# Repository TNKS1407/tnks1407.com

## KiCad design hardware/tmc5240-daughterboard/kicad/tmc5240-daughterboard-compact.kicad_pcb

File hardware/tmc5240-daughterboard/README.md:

# TMC5240 ステッピングモータ駆動 子基板 — 設計書 Rev.2a

JLCPCB 発注（PCBA、LCSC 在庫部品）前提。ホストは Raspberry Pi Pico（3.3V / SPI）。

**Rev.2 変更点:** エンコーダ後付け対応（J4 追加、ENCA/B/N を GND 直結→ヘッダ＋10k プルダウンに変更）、UART_EN を GND 直結→ハンダジャンパ SJ1（既定 GND=SPI）に変更。

**Rev.2a 変更点（レイアウト確定に伴う）:**
- **KiCad 基板レイアウト完成**（`kicad/`、60×42mm 4層、**DRC エラー 0・未接続 0**）。製造データは `fab/`。
- **J1 ピン並び変更**: 7〜11 番を `REFL, REFR, ENN, DIAG0, DIAG1` の順に（配線交差の完全回避のため）。
- **J3 ピン並び変更**: `1:OUT1A, 2:OUT2A, 3:OUT2B, 4:OUT1B`（A1 A2 B2 B1）。コイルB の2線は太い配線を表層で交差なく引くための入替。結線はシルク表記に従えば従来と等価。
- C10〜C13（1nF EMC対策、DNP可）は**基板にパターンを設けない**判断とした（必要になった事例が出たら Rev.3 で追加）。

| 項目 | 値 |
|---|---|
| モータ | バイポーラ2相、定格 1.5 A/相、巻線 2.8 Ω |
| 電源 VS | 24 V 単一入力、想定最大 2 A |
| ホスト I/F | 4線 SPI（UART_EN = GND で選択） |
| VCC_IO | 3.3 V（Pico 3V3） |
| コイル電流 | 1.5 A RMS（R_IREF 12 kΩ + GLOBALSCALER=181 + IRUN=31） |
| モード | StealthChop2 ＋ StallGuard4 センサレス原点出し |
| 成果物 | `schematic.svg`（回路図）, `bom_jlcpcb.csv`（JLCPCB用BOM）, 本書 |

## Rev.0 ドラフトからの訂正（データシート・実設計クロスチェックの結果）

初版の一般論ベースの想定から、以下を**訂正**した。根拠は ADI 公式データシート（検索抽出）、公式 TMC-API レジスタ定義、および独立した2つの公開リファレンス設計（KiCad ネットリストを直接照合）。

1. **VSA ピンは存在しない** → VSA 用 RC/フェライトフィルタを削除。アナログ系は AGND ピンのみ分離。
2. **内蔵レギュレータは 1.8V コア（VDD1V8 ピン）**であり 5V ではない → 2.2 µF を AGND へ。出力専用・負荷接続禁止。
3. **チャージポンプのリザーバは VCP–VS 間 1.0 µF**（100nF ではない）。フライングは CPO–CPI 間 22 nF/50V。
4. **SD_MODE / SPI_MODE ピンは存在しない**。インターフェース選択は UART_EN のみ（GND=SPI）。STEP/DIR ピン自体が無い（内蔵ランプジェネレータ専用）。
5. **SLEEPN（内部プルダウン）を H に吊る必要がある**。唯一の高電圧トレラント制御ピン。本設計では 3V3 へ直結。
6. **CSN は内部プルダウン**（UART アドレスストラップ兼用）→ MCU ブート中の誤選択防止に 10 kΩ プルアップを追加。
7. RDSon 実測値（HS 0.12 Ω + LS 0.11 Ω @3A レンジ）により**損失見積を 2.7 W → 約 1.0〜1.5 W に下方修正**。
8. パッケージは **TQFN-32 5×5（TMC5240ATJ+）と TSSOP-38（AUU+）のみ**。TQFP32 は存在しない。JLCPCB 在庫があるのは TQFN-32 リール品。

## 1. 電流設計（計算根拠）

```
IFS = KIFS / R_IREF            KIFS: 1Aレンジ 11.75, 2Aレンジ 24, 3Aレンジ 36 [A·kΩ]
I_RMS = (GLOBALSCALER/256) × ((CS+1)/32) × IFS/√2
```

- 目標 1.5 A RMS → ピーク 1.5×√2 = **2.12 A** → 2A レンジ（最大 2.0 A ピーク）では不足 → **3A レンジ**。
- **R_IREF = 12 kΩ ±1%** → IFS = 36/12 = **3.0 A**（IREF ピン電圧 ≈0.9 V、許容 12–60 kΩ※下記「要確認」参照）。
- CS(IRUN) = 31 固定（CoolStep の動作余地を確保）、GLOBALSCALER で合わせ込み:
  `1.5 = (GS/256) × 1 × 3.0/√2 → GS = 256×0.7071 ≈ 181 (0xB5)` — 推奨帯 128–255 内。
- IFS 3.0 A はデバイス定格（2 A RMS / 3 A ピーク）の範囲内、運転 1.5 A RMS も連続定格内。

**レジスタ初期値（TMC-API 名）**

| レジスタ | 値 | 意味 |
|---|---|---|
| DRV_CONF.CURRENT_RANGE | 2 (=3A) | フルスケールレンジ |
| GLOBALSCALER | 181 | 3.0A×0.707 → 2.12A ピーク |
| IHOLD_IRUN.IRUN | 31 | 1.5 A RMS |
| IHOLD_IRUN.IHOLD | 10 | 保持 ≈0.5 A RMS（発熱低減、要調整） |
| GCONF.en_pwm_mode | 1 | StealthChop2 |
| GCONF.diag0_int_pushpull / diag1_poscomp_pushpull | 0 | オープンドレイン（外部10kプルアップ前提） |

## 2. 回路各部（`schematic.svg` 対応）

### ① 電源入力・保護
- J2(+24V) → F1 PPTC 3A/33V → Q1 P-MOSFET 逆接保護（D=入力, S=負荷, G=R8 10k→GND, D2 BZT52C12 で |VGS| を 12V にクランプ）→ VS。
- D1 SMBJ33A（33V standoff）で VS–GND をクランプ。C1 100 µF/35V バルク。
- Q1 は SOT-23 で −40V/−3A（60 mΩ）。24V系で −30V 品（AO3401A 等）は TVS クランプ時に耐圧不足になるため不可。電流余裕が欲しい場合は AOD4185（TO-252, −40V/−40A）へ差し替え。

### ② デカップリング
- VS: 1 µF + 100 nF を VS ピン2グループ（pin17 側 / pin20-21-24 側）の直近に各1組（C2/C4, C3/C5）。
- VCC_IO: 100 nF（C9）。VDD1V8: 2.2 µF（C8, AGND へ）。
- モータ出力 OUT1A/2A/1B/2B に 1 nF（C10–13, EMC対策, DNP可）。

### ③ チャージポンプ
- CPO–CPI: 22 nF/50V（C6）。VCP–VS: 1 µF（C7, **VS ピン直近に配置** — 誘導性ピーク回避のためデータシート指示）。

### ④ ロジック
- UART_EN → **SJ1（3パッドハンダジャンパ、既定 GND側ブリッジ = 4線SPI）**。3V3 側に付け替えると1線UARTモード。CLK=GND（内蔵発振 12.5 MHz ±5%、SPI クロック上限 10 MHz）。
- AIN 未使用 → GND。OV ピン未使用 → 開放（過電圧クランプFETは未実装）。
- プルアップ 10k×4: CSN / ENN(DRV_ENN) / DIAG0 / DIAG1（DIAG はオープンドレイン既定のため必須）。
- プルダウン 10k×2: REFL / REFR（未接続時のレベル確定。SW_MODE で極性設定可）。

### ⑤ エンコーダ（後付け対応）
- ENCA/ENCB/ENCN を J4（2.54mm 1×5: 3V3 / A / B / N / GND）へ引き出し。**未接続時は R9〜R11 の 10k プルダウンでレベル確定**（フロート禁止のため）。
- 対応エンコーダは **3.3V ロジック（VCC_IO ドメイン）の ABN インクリメンタル**。5V 出力品はレベル変換が必要。
- 使うときのレジスタ: `ENCMODE`(0x38) で極性/クリア条件、`ENC_CONST`(0x3A) にエンコーダ分解能↔マイクロステップ換算、実位置は `X_ENC`(0x39)。N チャネルで StallGuard 原点出しより高精度なホーミングも可能。

### UART について（設計判断）
- Pico と1対1の本構成では **SPI を正式採用**。全二重・10MHz・毎応答ステータス付きで、StealthChop2/StallGuard4 の全機能が使える。
- TMC5240 の UART は1線半二重で、利点は配線削減と多軸デイジーチェーン（CSN/SCK/SDI がアドレスストラップ AD2/AD1/AD0 兼用）。単基板では利点なし。
- ただし選択は UART_EN ピン1本なので、**SJ1 により追加部品ゼロで将来切替可能**にした。UART に切り替えた場合、J1 の SDI ピンが1線データ、CSN/SCK のプルアップ/プルダウン状態がノードアドレスになる点に注意。

### コネクタ

**J1 2.54mm 1×12（Pico 接続）**

| ピン | 信号 | Pico |
|---|---|---|
| 1 | GND | GND |
| 2 | 3V3 | 3V3(OUT) — VCC_IO 用。モータ電源とは別系統 |
| 3 | SCK | GP18 (SPI0 SCK) |
| 4 | SDI (MOSI) | GP19 (SPI0 TX) |
| 5 | SDO (MISO) | GP16 (SPI0 RX) |
| 6 | CSN | GP17 |
| 7 | REFL | 原点SW（任意） |
| 8 | REFR | 原点SW（任意） |
| 9 | ENN | 任意 GPIO（L=駆動許可） |
| 10 | DIAG0 | 任意 GPIO（割込/StallGuard） |
| 11 | DIAG1 | 任意 GPIO |
| 12 | GND | GND |

> ピン並びは Rev.2a レイアウトの配線順に合わせた確定値（交差回避）。

**J2** 5.08mm 2P: +24V / GND　**J3** 5.08mm 4P: `1:OUT1A / 2:OUT2A（コイルA）/ 3:OUT2B / 4:OUT1B（コイルB）`（シルク: A1 A2 B2 B1）

**J4 2.54mm 1×5（エンコーダ、後付け可）**

| ピン | 信号 | 備考 |
|---|---|---|
| 1 | 3V3 | エンコーダ電源（3.3V ロジック品のみ） |
| 2 | ENCA | A相 |
| 3 | ENCB | B相 |
| 4 | ENCN | N（インデックス） |
| 5 | GND | — |

## 3. ネットリスト

| ネット | 接続 |
|---|---|
| +24V_IN | J2.1, F1.1 |
| 24V_F | F1.2, Q1.D |
| VS | Q1.S, D2.K, D1.K, C1.+, C2.1, C3.1, C4.1, C5.1, C7.2, U1.17, U1.20, U1.21, U1.24 |
| Q1_G | Q1.G, R8.1, D2.A |
| 3V3 | J1.2, J4.1, U1.5(VCC_IO), U1.25(SLEEPN), R2.1, R3.2, R4.2, R5.2, C9.1, SJ1.3 |
| SCK | J1.3, U1.27 |
| SDI | J1.4, U1.28 |
| SDO | J1.5, U1.29 |
| CSN | J1.6, U1.26, R2.2 |
| ENN | J1.9, U1.9(DRV_ENN), R3.1 |
| DIAG0 | J1.10, U1.11, R4.1 |
| DIAG1 | J1.11, U1.12, R5.1 |
| REFL | J1.7, U1.31, R6.1 |
| REFR | J1.8, U1.32, R7.1 |
| ENCA | J4.2, U1.8, R9.2 |
| ENCB | J4.3, U1.7, R10.2 |
| ENCN | J4.4, U1.6, R11.2 |
| UART_EN | U1.10, SJ1.2（中央パッド） |
| IREF | U1.1, R1.2 |
| VDD1V8 | U1.3, C8.2 |
| CPO | U1.15, C6.2 |
| CPI | U1.14, C6.1 |
| VCP | U1.16, C7.1 |
| OUT1A | U1.23, J3.1 |
| OUT2A | U1.22, J3.2 |
| OUT2B | U1.19, J3.3 |
| OUT1B | U1.18, J3.4 |
| GND | J2.2, J1.1, J1.12, J4.5, D1.A, C1.−, C2–C5.2, C8.1(AGND経由), C9.2, R1.1, R6.2, R7.2, R8.2, R9.1, R10.1, R11.1, SJ1.1（既定ブリッジ側）, U1.2(AIN), U1.4(AGND), U1.30(CLK), U1.EP, H1–H3 |

## 4. 発熱見積

- 導通損: 2相 × 1.5² × (0.12+0.11) Ω ≈ **1.04 W**。スイッチング・コア込みで **約 1.3〜1.5 W**。
- **θJA 実値（自己レビューで確認）: TQFN32 = 29 ℃/W（4層 JEDEC 基板）/ 47 ℃/W（1層）、θJC 1.7 ℃/W**。
  - Rev.2a（60×42, 4層）: JEDEC 基板よりやや小さいので実効 30〜38 ℃/W → ΔT ≈ 40〜55 ℃、室温で Tj ≈ 75〜80 ℃ ✓
  - Rev.2b（50×36, 4層）: 実効 ~40〜47 ℃/W → ΔT ≈ 55〜65 ℃。1.5A RMS 連続は成立圏内だが余白薄
- いずれも **EP 直下サーマルビア9本＋GND ベタ**を実装済み。停止時は IHOLD=10 で電流を落とす。

## 5. レイアウト注意

- EP（露出パッド）= パワー GND。直下にサーマルビア ≥9 本、裏面ベタへ。
- C7（VCP–VS）と C6（CPO–CPI）は該当ピン直近・最短ループ。
- R1（IREF）はピン1直近、GND リターン最短、モータ配線から離す（電流精度に直結）。
- C2/C4 と C3/C5 は VS ピンの2グループにそれぞれ配置。C1 はその外側。
- AGND（pin4）と C8 のリターンは静かな GND 経由で EP ベタへ（モータ電流経路と分ける）。
- OUT 配線は太く短く。J2/J3（24V系）と J1（3.3V系）は物理的に分離。

## 5.5 KiCad レイアウト（Rev.2a、`kicad/` と `fab/`）

- **基板**: 60 × 42 mm、**4層**（L1: 信号＋GNDベタ / L2: GND 全面 / L3: 3V3＋VS プレーン＋GND / L4: 一部信号＋GNDベタ）。M2.5 マウント穴 ×3（GND接続）。
- **検証**: KiCad 7 DRC で **エラー 0・未接続パッド 0**（クリアランス 0.15mm、最小ビア 0.4/0.2 — JLCPCB 4層の標準能力内）。
- **生成方法**: `kicad/generate_pcb.py` が基板を完全生成（`python3 generate_pcb.py`）。手修正せずスクリプトを変更して再生成する運用。
- **主要配置**: J1(Pico)左端 / J2(24V)上左 / 保護回路（F1→Q1→D1→C1）上辺 / U1 中央（EP 直下サーマルビア9本） / J3(モータ)右端 / J4(エンコーダ)＋SJ1 下辺。
- **電源**: 24V入力 2.0mm 幅、モータ出力はエスケープ 0.25→0.5→1.0mm 段階拡幅、VS/3V3 は内層プレーン給電。
- **`fab/` の内容**:
  - `tmc5240-daughterboard_gerbers.zip` — JLCPCB にそのままアップロードする製造データ（4層）
  - `bom_jlcpcb_pcba.csv` / `cpl_jlcpcb.csv` — PCBA 用 BOM・配置データ
- **発注手順**: ①zip をアップロード → 4 Layers を確認 ② PCBA(Economic) を選択、BOM/CPL を投入 ③ 部品照合で **U1 の在庫確保**と**回転（特に U1/Q1/D1/D2 の向き）を必ずプレビューで確認**（KiCad→JLCPCB の回転規約差は要目視）。
- **PCBA 対象外**: J4（C番号未確定 → 手半田推奨）、SJ1（銅箔のみ）、H1–H3（穴）。J1/J2/J3 は THT — Economic PCBA の THT 対応か手半田かを選択。

## 5.6 Rev.2b コンパクト版（50×36mm、`kicad/generate_pcb_compact.py`）

Rev.2a（60×42）の**トポロジ・回路・J1/J3 ピン配列をそのまま**に、面積を −50% した派生版。**KiCad 7 DRC エラー 0・未接続 0**。

- **サイズの意味**: JLCPCB の**4層最安ティア（50×50mm 以内）に収まる**。60mm 幅の Rev.2a はティア超えだったため、小型化がそのままコストダウンになる
- **全配線 45° 面取り**（`track()` ヘルパーが直角コーナーを自動チャンファ）
- 変更点: D1(TVS) は J3 上の空き地へ移動（SMBJ33A のまま）、マウント穴は M2×2（右下・左下）、C10–13 相当は引き続き非実装
- **放熱トレードオフ**: 銅面積半減で θJA ≈ 45 K/W 見込み（Rev.2a 比 +10）。1.5A RMS 連続は成立圏内だが余白減。**IHOLD 低減運用を推奨**、連続高負荷なら Rev.2a を選ぶ
- 製造データ: `kicad/fab-compact/`（ガーバー zip / BOM / CPL）。どちらを発注するかで `fab/`（Rev.2a）と使い分け

## 6. JLCPCB 発注メモ

- **U1 の在庫が薄い**（2026-07 時点 約240個）→ 発注前に JLCPCB のプライベートライブラリで部品確保推奨。
- TMC2240（C7429724, 在庫潤沢・安価）は**ピン互換ではない**（STEP/DIR 型でランプジェネレータ非搭載）。代替にする場合は回路・ソフト両方の再設計が必要。
- パッシブはほぼ Basic 部品（実装費安）。Extended は U1/Q1/D1/D2/F1/C1/コネクタ類。
- J1/J2/J3 は THT → JLCPCB の「Standard PCBA (THT対応)」を選択するか、手半田にするなら BOM から除外。
- Basic/Extended 区分と在庫は変動する。**発注直前に JLCPCB の BOM ツールで再確認**。

## 7. 設計レビュー チェックリスト

- [ ] R_IREF=12kΩ 1% / CURRENT_RANGE=3A / GLOBALSCALER=181 / IRUN=31 → 1.5 A RMS の整合
- [ ] CPO–CPI 22nF・VCP–VS 1µF がピン直近か
- [ ] VDD1V8 に 2.2µF（AGND へ）、負荷を繋いでいないか
- [ ] SLEEPN が 3V3 に接続されているか（内部プルダウンのため開放不可）
- [ ] SJ1 が GND 側ブリッジ（SPI）で製造されるか（銅箔ブリッジ or 製造時ハンダ指示）、CLK=GND（内蔵OSC）か
- [ ] DIAG0/1・CSN・ENN に 10k プルアップ、REFL/REFR・ENCA/B/N に 10k プルダウン
- [ ] エンコーダは 3.3V ロジック品か（5V 品はレベル変換要）
- [ ] TVS クランプ電圧が VS 絶対最大（38V）を超える条件を理解しているか（§8 参照。大回生用途は OV クランプ追加）／Q1 耐圧 −40V 以上か
- [ ] EP サーマルビア・GND ベタ・IHOLD 低減の放熱3点セット
- [ ] 発注直前の在庫・Basic/Extended 再確認（特に U1）

## 8. 自己レビュー結果（2026-07-02 実施）と残る未確認事項

データシート PDF 原本は取得経路が全て遮断されたため、**到達可能な一次情報での機械照合レビュー**を実施した。使用ソース: ADI 公式レジスタ定義（TMC-API `TMC5240_HW_Abstraction.h`）、Klipper 公式ドライバ（`tmc2240.py`、同一電流アーキテクチャ）、独立した実設計3ソースのシンボル/回路図（RPZ-Stepper 系 .kicad_sym、equilibot、MIT MediaLab pan-tilt）。

### 検証済み（機械照合で確認）

| 項目 | 結果 |
|---|---|
| U1 ピン配置（33ピン） | **3つの独立ソースと全一致**（スクリプトで pin番号→名称を突き合わせ） |
| 電流設定式 | Klipper 実装と完全一致: `KIFS=[11.75,24,36]A·kΩ`, `I_RMSmax=KIFS/Rref/√2`, `GS=round(256·I/I_RMSmax)` → **12kΩ+3Aレンジ+GS=181 で 1.500A RMS（丸めまで一致）**。Rref=12kΩ は Klipper の既定値でもある |
| GLOBALSCALER 制約 | 公式ヘッダ記載と一致（1–31 禁止、>128 推奨、0=フルスケール） |
| 標準回路定数 | 22nF(CPO–CPI)・2.2µF(VDD1V8)・1µF(VCP)・IREF 12k/13k を実設計2件で確認 |
| **θJA/θJC 実値** | TQFN32: **29 ℃/W（4層 JEDEC 基板）/ 47 ℃/W（1層）、θJC 1.7 ℃/W**。§4 の見積（35〜45）は安全側で妥当 |
| VS 絶対最大 | **38 V**（絶対最大表の断片「CPO ≤ min(44, VS+6)V」の44上限から逆算、姉妹品 TMC2240=38V とも一致。直接記載の確認は未） |
| Rev.2a ⇔ Rev.2b | 全112パッドのネット割当を diff、**電気的に同一**（差分は H3 削除と R2 のパッド順のみ＝抵抗なので無影響） |
| Q1 ピン配置 | SOT-23 単体 P-MOSFET は業界横断で 1=G/2=S/3=D（ST/onsemi/MCC で確認）。基板はこの通り |

### レビューで見つかった問題（正直に）

**⚠ TVS（SMBJ33A）は高エネルギーサージに対して完全ではない。** VS 絶対最大 38V に対し、SMBJ33A のクランプ電圧は定格サージ電流時 **最大 53.3V** — ESD や小サージには有効だが、大きな誘導性サージ／モータ回生では 38V を超えるおそれがある。スタンドオフを下げても（SMBJ30A 等）クランプは 38V を下回らないため、**TVS 単体では構造的に解決しない**（36V級ドライバ＋24V系の一般的な妥協点）。データシートが想定する本来の対策は **OV ピン＋外付け N-FET クランプ**（MIT MediaLab 設計は実装済み、本設計は未実装・OV開放）。

**運用条件**: 安定化24V電源・回生エネルギー小（通常のNEMA17位置決め用途）なら現状で実用可。長い減速で大きな回生が出る用途・電源が不安定な環境では **Rev.3 で OV クランプ回路（N-FET+抵抗2本+ショットキー）の追加を推奨**。

### 残る未確認（PDF 原本が読めたら潰す）

1. VS 絶対最大 38V の直接記載確認（傍証は強い）
2. R_IREF 許容帯の正式値（12–60k か 12–24k か。12kΩ はどちらでも適合）
3. S-LP2408LT1G 固有データシートのピン配置（業界慣例とは一致）
4. C10–13 用 C1588 の Basic 区分

### 根拠資料

- [TMC5240 データシート (ADI)](https://www.analog.com/media/en/technical-documentation/data-sheets/tmc5240.pdf)（検索抽出）
- [TMC-API TMC5240 レジスタ定義 (ADI 公式 GitHub)](https://github.com/analogdevicesinc/TMC-API/blob/master/tmc/ic/TMC5240/TMC5240_HW_Abstraction.h)
- [電流設定の考え方 (ADI EngineerZone)](https://ez.analog.com/other-products/w/documents/32673/)
- リファレンス設計: [benjibst/equilibot](https://github.com/benjibst/equilibot), [mitmedialab/generic-pan-tilt-pcb](https://github.com/mitmedialab/generic-pan-tilt-pcb)（KiCad ネットリスト照合）
- [TMC5240ATJ+T @LCSC C7494373](https://www.lcsc.com/product-detail/Motor-Driver-ICs_TRINAMIC-Motion-Control-GmbH-TMC5240ATJ-T_C7494373.html) / [@JLCPCB](https://jlcpcb.com/partdetail/8557215-TMC5240ATJT/C7494373)

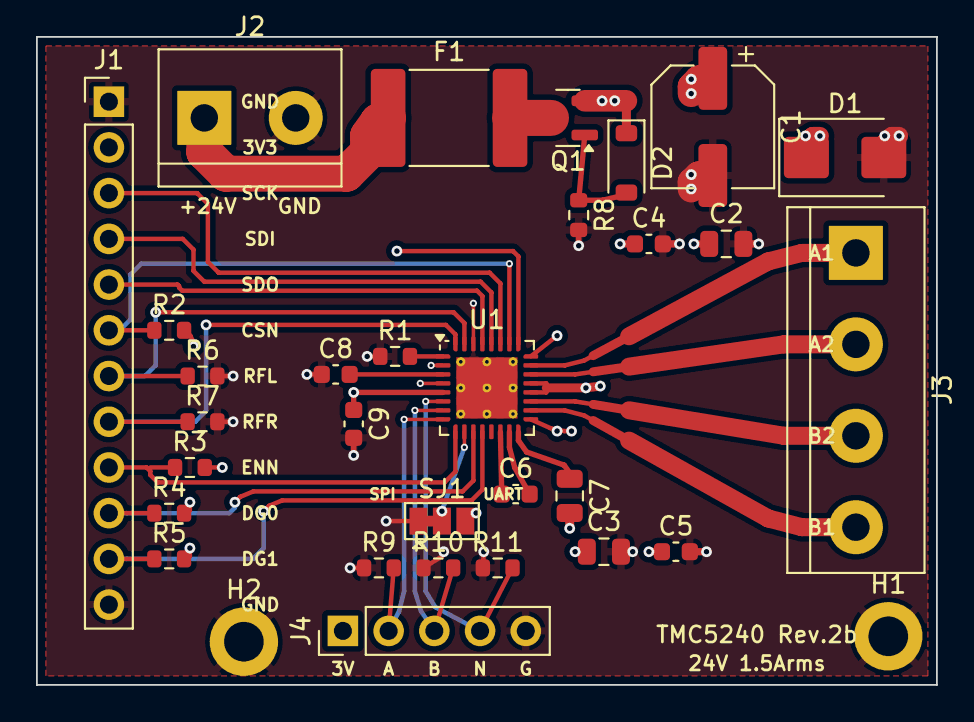
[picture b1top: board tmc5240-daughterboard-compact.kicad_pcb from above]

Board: 4 copper layers, 50.0 x 36.0 mm, 32 parts (0 on the bottom side), 28 nets.

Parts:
C1: 100uF/35V; CP_Elec_6.3x7.7
C2, C3, C7: 1uF/50V; C_0805_2012Metric
C4, C5: 100nF/50V; C_0603_1608Metric
C6: 22nF/50V; C_0603_1608Metric
C8: 2.2uF; C_0603_1608Metric
C9: 100nF; C_0603_1608Metric
D1: SMBJ33A; D_SMB
D2: BZT52C12; D_SOD-123
F1: PPTC 3A/33V; Fuse_2920_7451Metric
H1, H2: M2; MountingHole_2.2mm_M2_DIN965_Pad
J1: Pico 1x12; PinHeader_1x12_P2.54mm_Vertical
J2: +24V IN; TerminalBlock_bornier-2_P5.08mm
J3: MOTOR; TerminalBlock_bornier-4_P5.08mm
J4: ENC 1x5; PinHeader_1x05_P2.54mm_Vertical
Q1: S-LP2408LT1G; SOT-23
R1: 12k 1%; R_0603_1608Metric
R2, R3, R4, R5, R6, R7, R8, R9, R10, R11: 10k; R_0603_1608Metric
SJ1: SPI/UART; SolderJumper-3_P1.3mm_Bridged12_Pad1.0x1.5mm
U1: TMC5240ATJ+T; TQFN-32-1EP_5x5mm_P0.5mm_EP3.4x3.4mm_ThermalVias

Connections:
3V3: C9.1, J1.2, J4.1, R2.2, R3.2, R4.2, R5.2, SJ1.3, U1.5, U1.25
24V_F: F1.2, Q1.3
+24V_IN: F1.1, J2.1
CPI: C6.1, U1.14
CPO: C6.2, U1.15
CSN: J1.6, R2.1, U1.26
DIAG0: J1.10, R4.1, U1.11
DIAG1: J1.11, R5.1, U1.12
ENCA: J4.2, R9.2, U1.8
ENCB: J4.3, R10.2, U1.7
ENCN: J4.4, R11.2, U1.6
ENN: J1.9, R3.1, U1.9
GND: C1.2, C2.2, C3.2, C4.2, C5.2, C8.1, C9.2, D1.2, H1.1, H2.1, J1.1, J1.12, J2.2, J4.5, R1.1, R6.2, R7.2, R8.2, R9.1, R10.1, R11.1, SJ1.1, U1.2, U1.4, U1.30, U1.33
IREF: R1.2, U1.1
OUT1A: J3.1, U1.23
OUT1B: J3.4, U1.18
OUT2A: J3.2, U1.22
OUT2B: J3.3, U1.19
Q1_G: D2.2, Q1.1, R8.1
REFL: J1.7, R6.1, U1.31
REFR: J1.8, R7.1, U1.32
SCK: J1.3, U1.27
SDI: J1.4, U1.28
SDO: J1.5, U1.29
UART_EN: SJ1.2, U1.10
VCP: C7.1, U1.16
VDD1V8: C8.2, U1.3
VS: C1.1, C2.1, C3.1, C4.1, C5.1, C7.2, D1.1, D2.1, Q1.2, U1.17, U1.20, U1.21, U1.24

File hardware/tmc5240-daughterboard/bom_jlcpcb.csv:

Comment,Designator,Footprint,LCSC Part #,Basic/Extended,Notes
"TMC5240ATJ+T stepper driver",U1,TQFN-32_5x5mm_EP,C7494373,Extended,"在庫薄(~240個@2026-07)。早めに確保。代替: C7429725(トレイ品)"
"S-LP2408LT1G P-MOSFET -40V -3A",Q1,SOT-23,C5273674,Extended,"逆接保護。余裕が欲しければ AOD4185 (TO-252) C400894"
"SMBJ33A TVS 33V standoff",D1,SMB(DO-214AA),C78419,Extended,"代替: SMBJ36A C114001"
"BZT52C12 zener 12V",D2,SOD-123,C43491,Extended,"Q1ゲート-ソース保護"
"PPTC 3A hold 33V",F1,2920,C6165175,Extended,"1812で3A/30V品は未確認 → 2920採用"
"100uF 35V SMD electrolytic",C1,SMD_6.3x8mm,C2827942,Extended,"Basic該当なし。代替: C165580 (8x10mm)"
"1uF 50V X7R",C2 C3,0805,C28323,Basic,"VSピン2グループ直近に分置"
"100nF 50V X7R",C4 C5 C9,0603,C14663,Basic,"VS×2 + VCC_IO"
"22nF 50V X7R",C6,0603,C21122,Basic,"チャージポンプ フライングキャパシタ CPO-CPI"
"1uF 50V X7R",C7,0805,C28323,Basic,"VCP-VS リザーバ。VSピン直近に配置"
"2.2uF 16V X5R",C8,0603,C23630,Basic,"VDD1V8(内蔵1.8Vコア)用。AGNDへ"
"1nF 50V X7R (DNP可)",C10 C11 C12 C13,0603,C1588,Basic(要確認),"モータ出力EMC対策。Rev.2aレイアウトではパターン未実装（必要ならRev.3で追加）"
"12k 1% (IREF)",R1,0603,C22790,Basic,"電流設定。1%必須"
"10k 1%",R2 R3 R4 R5 R6 R7 R8 R9 R10 R11,0603,C25804,Basic,"プルアップ/プルダウン/ゲート/ENC未接続時確定"
"Pin header 1x12 2.54mm",J1,THT_1x12_2.54mm,C124353,Extended,"Ckmtw B-2101S12P-A110。フットプリント要確認"
"Screw terminal 2P 5.08mm",J2,THT_5.08mm_2P,C8465,Extended,"Kangnex WJ500V-5.08-2P (在庫潤沢)"
"Screw terminal 4P 5.08mm",J3,THT_5.08mm_4P,C430599,Extended,"DORABO DB128L-5.0-4P (Kangnex 4Pは在庫僅少のため変更)"
"Pin header 1x5 2.54mm",J4,THT_1x5_2.54mm,要確認,Extended,"エンコーダ(ABN 3.3V)後付け用。Ckmtw C1243xx系で1×5を検索。手半田でも可"
"Solder jumper 3-pad",SJ1,SolderJumper_3_Open+Bridged,-,-,"銅箔のみ・部品なし。既定GND側ブリッジ=SPI、3V3側=UART"

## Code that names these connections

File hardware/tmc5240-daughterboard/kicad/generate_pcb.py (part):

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J1 pin order chosen for crossing-free escape:
  1 GND, 2 3V3, 3 SCK, 4 SDI, 5 SDO, 6 CSN, 7 REFL, 8 REFR,
  9 ENN, 10 DIAG0, 11 DIAG1, 12 GND
J3 pin order: 1 OUT1A, 2 OUT2A, 3 OUT2B, 4 OUT1B (A1 A2 B2 B1)

Run:  python3 generate_pcb.py
"""
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C8 = cap0603("C8", "2.2uF",     19.9, 21.25, 0, "GND", "VDD1V8")   # pad2 right -> pin3
C9 = cap0603("C9", "100nF",     21.0, 24.0, -90, "3V3", "GND")     # pad1 up

R1  = res0603("R1", "12k 1%", 22.9, 20.25, 0, "GND", "IREF")       # pad2 right, inline pin1
R2  = res0603("R2", "10k", 6.6, 15.2, -90, "3V3", "CSN")   # pad1 up
R3  = res0603("R3", "10k", 8.5, 25.32, 0, "ENN", "3V3")
R4  = res0603("R4", "10k", 7.35, 27.86, 0, "DIAG0", "3V3")         # pad1 left -> J1.10
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track("3V3", [p[5], (21.0, p[5][1])], 0.3); via("3V3", 21.0, p[5][1])
track("3V3", [P(C9,1), (21.0, p[5][1])], 0.3)
track("GND", [P(C9,2), (21.0, 25.75)], 0.3); via("GND", 21.0, 25.75)
for pin, net, vx in [(6, "ENCN", 24.6), (7, "ENCB", 24.0), (8, "ENCA", 23.4)]:
    track(net, [p[pin], (vx, p[pin][1])], 0.2)
    via(net, vx, p[pin][1], 0.4, 0.2)
track("ENCN", [(24.6, p[6][1]), (24.6, 36.4), (P(J4,4)[0], 38.5)], 0.25, B)
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via("VS", 34.3, 22.0); via("VS", 35.1, 21.9)
track("VS", [p[17], (31.5, 24.5), (32.3, 24.5)], 0.25)
via("VS", 31.5, 24.5); via("VS", 32.3, 24.5)
for pin, net, jpin in [(23, "OUT1A", 1), (22, "OUT2A", 2), (19, "OUT2B", 3), (18, "OUT1B", 4)]:
    src = p[pin]
    tgt = P(J3, jpin)
    yat = lambda x: src[1] + (tgt[1] - src[1]) * (x - 33) / (52 - 33)
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    t.SetTextThickness(FromMM(0.15))
    board.Add(t)

labels = ["GND", "3V3", "SCK", "SDI", "SDO", "CSN", "RFL", "RFR", "ENN", "DG0", "DG1", "GND"]
for i, lab in enumerate(labels):
    silk(lab, 6.9, 5 + 2.54 * i, 0.7)
for i, lab in enumerate(["A1", "A2", "B2", "B1"]):
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
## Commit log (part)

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2026-06-02 Initial portfolio site
2026-06-02 Add Cloudflare Workers configuration
2026-06-02 Redesign with pastel theme
2026-06-02 Add nico-comment-system and tnks-lab to portfolio
2026-06-02 Add Shinku Tinks to portfolio
2026-06-02 Add roaming Tinks sprite to portfolio
2026-06-02 Add Vortex Generator Tools to portfolio
2026-06-02 Make Tinks sprite responsive (smaller on mobile)
2026-06-02 Add event-accounting-tool to portfolio
2026-06-02 Add VG Generator and events viewer to portfolio
2026-06-02 Redesign: compact hero, quick links bar, icon cards
2026-06-02 Add SEIGOU RF matching app
2026-06-02 Smaller Tinks, events admin quick link, click-to-wave
2026-06-02 Add PSU workbench and Graph Workbench
2026-06-02 Add FDTD app, prompt buttons for all works
2026-06-02 Fix prompt modal: use window.openPrompt for global scope
2026-06-02 Add MOSFET guide to portfolio
2026-06-02 Add playful elements: sparkle trail, Tinks escape/time-quips, Konami code, hero avatar click
2026-06-02 Add hidden memo page
2026-06-03 fix: label Nico admin link as auth-required
2026-06-03 feat: add Process Modeling Lab (pml.tnks1407.com)
2026-06-05 Stop tracking dev-server logs
2026-06-05 FDTD: fix Streamlit tag (now self-hosted python server)
2026-06-05 Add Stepper Physics Lab to portfolio (stepper.tnks1407.com)
2026-06-05 Update Rankine sprite: researcher outfit (v2)
2026-06-05 Fix Rankine sprite: remove magenta key fringe (despill)
2026-06-06 Sprite: adopt Codex-refined researcher design (despilled)
2026-06-06 Add per-work favorite (star) buttons to portfolio
    Same one-per-person model as the blog (localStorage + server IP dedup),
    keyed by subdomain (or github repo name) as w-<label>.
2026-06-06 Security: escape feedback type/message (stored XSS); cap counter keys; fdtd path-traversal guard
2026-06-06 Add Reaction-Diffusion Lab (rd.tnks1407.com) to portfolio
2026-06-10 A第3歩: tnks1407クイックリンクの展開部をカテゴリ分け(エンジ/データ・画像/運用)で整理
2026-06-10 新ツール: 色空間3Dビューア /color (Three.js, HSL色立体ドラッグ回転+中立軸+色相環+ねじれ/ゆがみ)＋導線
2026-06-10 色空間3D改良: 丸み(球状)トグル/点数増/スライス可視化(濃い+ティール縁)/背景切替(暗黒白灰)
2026-06-10 色空間3D: スライス面を色付き断面に(その明度の色そのもの=中心グレー・外周で彩度最大・色相一周)
2026-06-11 PixLab: ランキン顔プリセットをもっとアップに(顔中心の正方形クロップでフレームいっぱい)
2026-06-11 PixLab: ランキン顔プリセットを指定の頭寄り構図に(本を外し襟・ブローチまで)
2026-06-11 PixLab/1D: 「詳しく」リンクをGradus教科書(textbook.html)へ向ける。触る=PixLab/読む=Gradus教科書 の役割分担を導線に反映
2026-06-11 トップWorks: Stepper選定シミュレータの説明を大改修版に更新＋画像処理ラボ PixLab を追加(/pixlab/、学びの道で1D/Gradus/教科書へ)
2026-06-11 PixLab: 演算「勾配の大きさ(横²+縦²)」を追加。Gx(Sobel横)とGy(Sobel縦)を両方計算→√(Gx²+Gy²)で向き問わず輪郭を抽出、明るさ面で1枚グレー出力(Gradusの輪郭抽出と同じ考え方)。既存演算は一切削らず追加のみ。ステップでGx/Gy両行列＋合成を表示
2026-06-11 色空間ビューア: 中立軸が見えない問題を修正。THREE.Line(WebGLで常に1px=細すぎ)→太さのあるTubeGeometryの芯に(ゆがみ曲線にも沿う)
2026-06-11 色空間ビューア 中立軸: ①黒(下/L=0)→白(上/L=1)のグラデーション着色(灰色一色をやめ明度の芯だと分かるように) ②スライダで軸が消えるバグ修正(axisDots=Groupに.geometry.dispose()して例外→再構築中断してた→traverse破棄に) ③depthTest:falseで雲に隠れず常に見える
2026-06-11 色空間ビューア: コントロールパネルを折りたたみ可能に(ヘッダーの▾/▸ボタン)。狭い画面(スマホ)は最初からたたんでビューを広く
2026-06-11 色空間ビューア: 「色空間の見かた（解説）」を折りたたみ式で常設(色空間とは/読み方/中立軸/色相環S¹/ねじれ=ベゾルト・ブリュッケ/ゆがみ/双円錐になる理由)。後で見返せるリファレンスに
2026-06-12 ステータス見直し: PixLabをBeta→Stableに昇格(昨日の大幅な磨き込みで完成・安定の域)
2026-06-15 docs(crystal): 第4記事「心(centering)」＋心widget(P/C/I/F→192)
2026-06-15 docs(crystal): 第5記事「実結晶 ── 岩塩を部品から組み立てる」＋本物の3Dエクスプローラー埋め込み(192→4特殊位置)
2026-06-15 docs(crystal): 編集レビュー反映 ── 周期結晶への限定/反転の整理(2D点対称=det+1)/W=[[a,b],[c,d]]統一/2cosθはベクトル和/n≥7は1<2cos<2/192=一般位置の等価点(空間群は無限)/中心化並進/底心/特殊位置・multiplicity/準結晶史1982-1984-2011/エクスプローラは教材用。補足ボックス追加。widget(mirror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
2026-06-15 docs(crystal): 第4.5回「空間群は圧縮ファイル」(効能=生成/Wyckoff/回折の指紋/物性の制約) ＋ 系統的消滅widget(P/C/I/F→消える hkl)
2026-06-15 docs(crystal): 記号を初出で定義(x',y'=写った先/プライムの意味/a,b,c,d/X,X',w,t,X''/hkl)。再定義は冗長でなく親切
2026-06-15 docs: 「読めなくても大丈夫」の定型文をやめ、毎回ちがう言い方に。向きも『読めないあなたへ』→『見た目ほど難しくない/要点をすぐ渡す』へ(上から目線を避ける)
2026-06-15 docs(crystal): 「5だけ弾かれる」は不正確(7・8も禁制)→「許されるのは1,2,3,4,6だけ」と先回り訂正。mirrorリンクも修正
2026-06-15 docs(crystal): 第6回フィナーレ「準結晶 ── 並進を捨てると5回が戻る」＋本物のペンローズwidget(正準デフレーション/φ収束)。結晶と対称シリーズ完結
2026-06-15 feat(waves): 共鳴管に「粗密」モード追加 ── 管内の空気の密度分布を青(密)/橙(疎)でシェーディング＋粒の前後。変位/圧力/粗密の3択に。スミスチャート的な線グラフだけでなく実際の粗密が見える
2026-06-16 tools: pf-tool.js は feedback-api (feedback.tnks1407.com/pf-tool.js) でホストするため portfolio から除去（重複回避・即時更新）
2026-06-24 ch4-2: fill in the gaps (行間) for accessibility, keep rigor
    - expand W=1/2mv^2 derivation step-by-step (dx=v dt, integral v dv)
    - altitude analogy for potential-energy-as-scalar-map
    - define volt as J/C with concrete numbers
    - explain dot product in integral E.dl (along-path component)
    - show antiderivative step in point-charge V integral
    No 'for beginners' framing; level kept, spacing/steps added.
2026-06-24 gauss-symmetry widget: 3D rendering (depth) per feedback
    - sphere: silhouette + lat/long ellipses (front solid/back dashed) + radial shading
    - cylinder: elliptical caps + curved-side shading
    - box: isometric cuboid (front solid, back dashed) straddling the charged sheet
    - drag to spin the view; physics (arrows, flux-constant readout) unchanged
    Verified sphere & box render via headless screenshot.
2026-06-24 gauss-symmetry: fix text overlap on mobile + polish cylinder/box
    - hint moved to bottom (no longer collides with top-right readout)
    - shape centered below a reserved top zone, scaled to fit viewport (no clipping on tall/mobile)
    - area labels moved below each shape
    - cylinder: solid top cap fill; box: subtle face fills for solidity
    - readout compacted (nowrap, shorter lines)
2026-06-24 workshop: add visible 作業ログ (per-agent activity, seeded with today's 2) — transparency per user request
2026-06-24 workshop log: first persistent maker デューイ(司書) — built memory map (39 memories into 9 shelves)
2026-06-30 widget(tof): correct sensor name to VL53L5CX (the unit actually purchased; both are 8x8)
